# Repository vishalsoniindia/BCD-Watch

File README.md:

# BCD-Watch

Youtube :- https://www.youtube.com/watch?v=fd1oudY0hw8

Buy it :- https://www.tindie.com/products/vishalsoniindia/bcd-watch-binary-coded-decimal/

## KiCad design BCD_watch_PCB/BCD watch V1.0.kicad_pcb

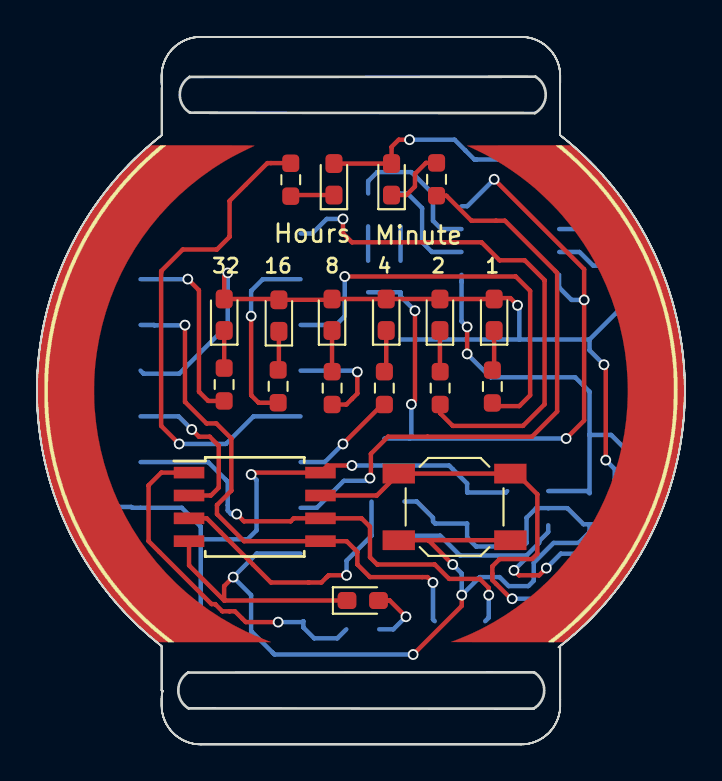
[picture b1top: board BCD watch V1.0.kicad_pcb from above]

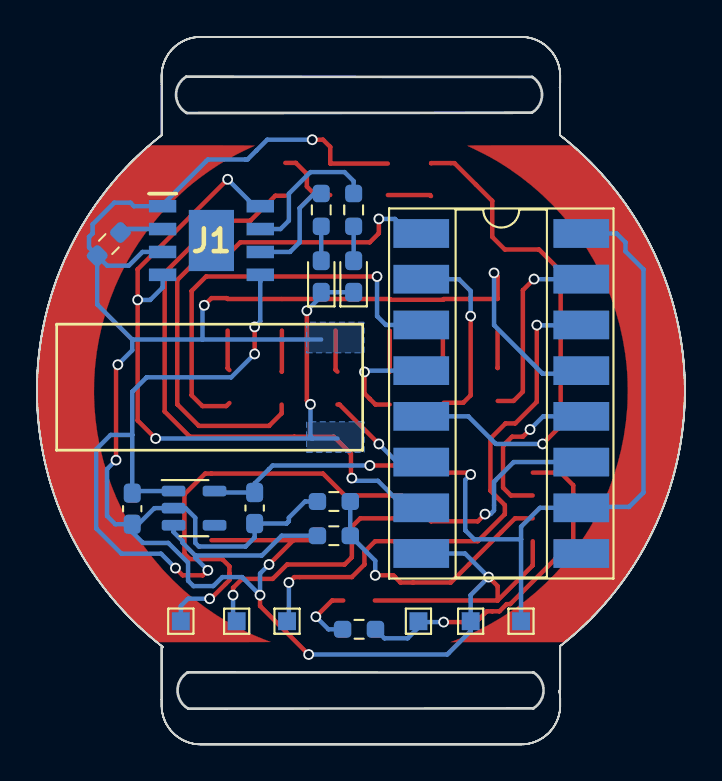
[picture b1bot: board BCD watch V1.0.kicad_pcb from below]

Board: 2 copper layers, 35.9 x 39.3 mm, 38 parts (19 on the bottom side), 32 nets.

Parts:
C1, C2: 100nf; C_0603_1608Metric_Pad1.08x0.95mm_HandSolder
D1, D2, D3, D4, D5, D6, D7, D8, D9, D10, D11: LED; LED_0603_1608Metric_Pad1.05x0.95mm_HandSolder
J1: TP4056; SOIC127P600X175-9N
R1, R2, R3, R4, R5, R6, R7, R8, R9, R11, R12: 220; R_0603_1608Metric_Pad0.98x0.95mm_HandSolder
R10: 1.2k; R_0603_1608Metric_Pad0.98x0.95mm_HandSolder
R13: 2k; R_0603_1608Metric_Pad0.98x0.95mm_HandSolder
R14: 5k; R_0603_1608Metric_Pad0.98x0.95mm_HandSolder
SW1: SW_Push; SW_SPST_SKQG_WithoutStem
TP1, TP2, TP3, TP4, TP5, TP6: TestPoint; TestPoint_Pad_1.0x1.0mm
U1: ATtiny85-20S; SOIC-8W_5.3x5.3mm_P1.27mm
U2: 74HC595; DIP-16_W8.89mm_SMDSocket_LongPads
U3: MIC5205-2.5YM5; SOT-23-5

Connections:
+3V3: C2.1, TP2.1, U1.8 (VCC), U2.10 (~SRCLR), U2.16 (VCC), U3.5 (OUT)
+BATT: C1.1, J1.5 (BAT), R13.2, U3.1 (IN), U3.3 (EN)
GND: C1.2, C2.2, D1.2 (A), D2.2 (A), D3.2 (A), D4.2 (A), D5.2 (A), D6.2 (A), D7.2 (A), D8.2 (A), D9.1 (K), J1.1 (TEMP1), J1.3 (GND_3), R10.1, R14.1, SW1.2, TP1.1, U1.4 (GND), U2.8 (GND), U2.13 (~OE), U3.2 (GND)
unnamed: D1.1 (K), R1.2
unnamed: D2.1 (K), R2.2
unnamed: D3.1 (K), R3.2
unnamed: D4.1 (K), R4.2
unnamed: D5.1 (K), R5.2
unnamed: D6.1 (K), R6.2
unnamed: D7.1 (K), R7.2
unnamed: D8.1 (K), R8.2
unnamed: D9.2 (A), R9.1
unnamed: D10.2 (A), R11.1
unnamed: D11.2 (A), R12.1
unnamed: J1.2 (PROG2), R10.2
unnamed: J1.6 (~STDBY), R11.2
unnamed: J1.7 (~CHRG), R12.2
unnamed: R1.1, U2.15 (QA)
unnamed: R2.1, U2.2 (QC)
unnamed: R3.1, U2.4 (QE)
unnamed: R4.1, U2.6 (QG)
unnamed: R5.1, U2.1 (QB)
unnamed: R6.1, U2.3 (QD)
unnamed: R7.1, U2.5 (QF)
unnamed: R8.1, U2.7 (QH)
unnamed: R9.2, TP6.1, U1.1 (~RESET/PB5)
unnamed: SW1.1, TP5.1, U1.7 (PB2)
unnamed: TP3.1, U1.5 (AREF/PB0), U2.14 (SER)
unnamed: TP4.1, U1.6 (PB1), U2.11 (SRCLK)
unnamed: U1.2 (XTAL1/PB3), U2.12 (RCLK)
VBUS: D10.1 (K), D11.1 (K), J1.4 (VCC4), J1.8 (CE)
volt: R13.1, R14.2, U1.3 (XTAL2/PB4)
